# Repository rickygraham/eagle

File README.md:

# eagle
A collection of Eagle libraries and sketches!

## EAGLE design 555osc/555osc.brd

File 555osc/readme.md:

#555 Astable Oscillator

Based on 555 Timer Kit by Synthrotek

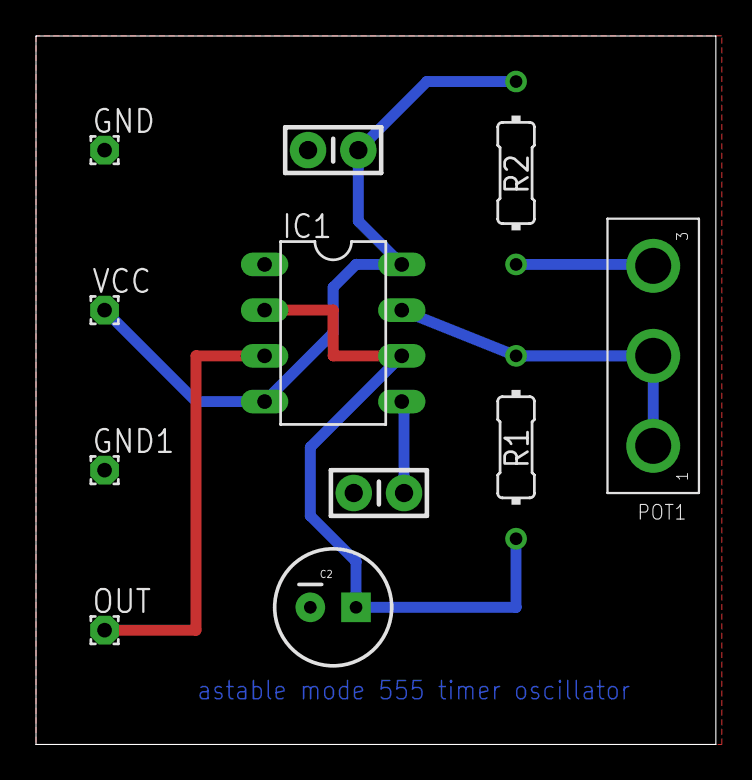
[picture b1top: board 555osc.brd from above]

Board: 2 copper layers, 37.8 x 39.4 mm, 11 parts (0 on the bottom side), 7 nets.

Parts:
C1, C3: CAP-PTH-SMALL-KIT
C2: CPOL-RADIAL-100UF-25V
GND, GND1: 1,6/0,8
IC1: ICM7555; DIL08
OUT: 1,6/0,8
POT1: POT
R1, R2: 3MM.3; RESISTOR
VCC: 1,6/0,8

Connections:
9V: C3.1, IC1.4, IC1.8, R2.2, VCC.1
GND: C1.2, C2.2, C3.2, GND.1, GND1.1, IC1.1
unnamed: POT1.3, R2.1
unnamed: C2.1, IC1.2, IC1.6, R1.1
unnamed: C1.1, IC1.5
unnamed: IC1.3, OUT.1
unnamed: IC1.7, POT1.1, POT1.2, R1.2

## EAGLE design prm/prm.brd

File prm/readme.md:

#Passive Ring Modulator

Based on Synthrotek kit:

http://www.synthrotek.com/products/lo-fi-synthesizer-circuits/passive-ring-modulator/passive-ring-mod-schematic/

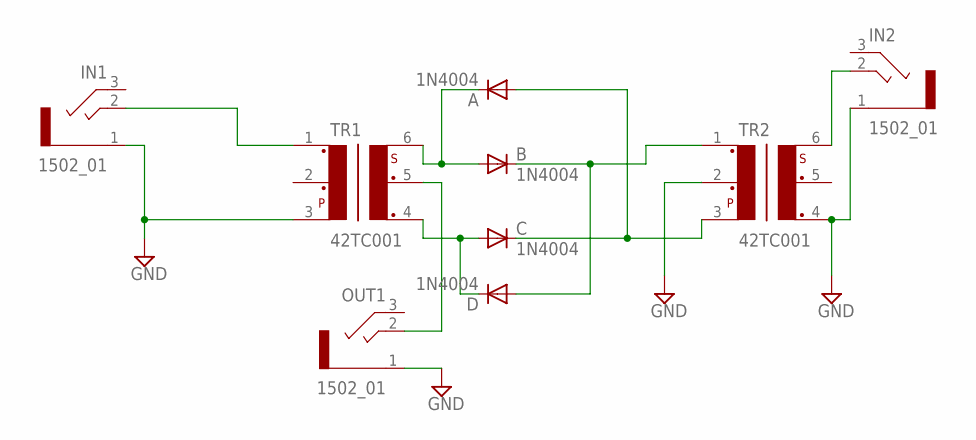
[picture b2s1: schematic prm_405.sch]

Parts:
A: 1N4004; DO41-10
B: 1N4004; DO41-10
C: 1N4004; DO41-10
D: 1N4004; DO41-10
IN1, IN2: 1502_01
OUT1: 1502_01
TR1, TR2: 42TC001; 42TC

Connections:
A: A.C, B.A, TR1.6
GND: IN1.1, IN2.1, OUT1.1, TR1.3, TR2.2, TR2.4
unnamed: IN1.2 (3), TR1.1
unnamed: OUT1.2 (3), TR1.5
unnamed: B.C, D.A, TR2.1
unnamed: A.A, C.C, TR2.3
unnamed: C.A, D.C, TR1.4
unnamed: IN2.2 (3), TR2.6

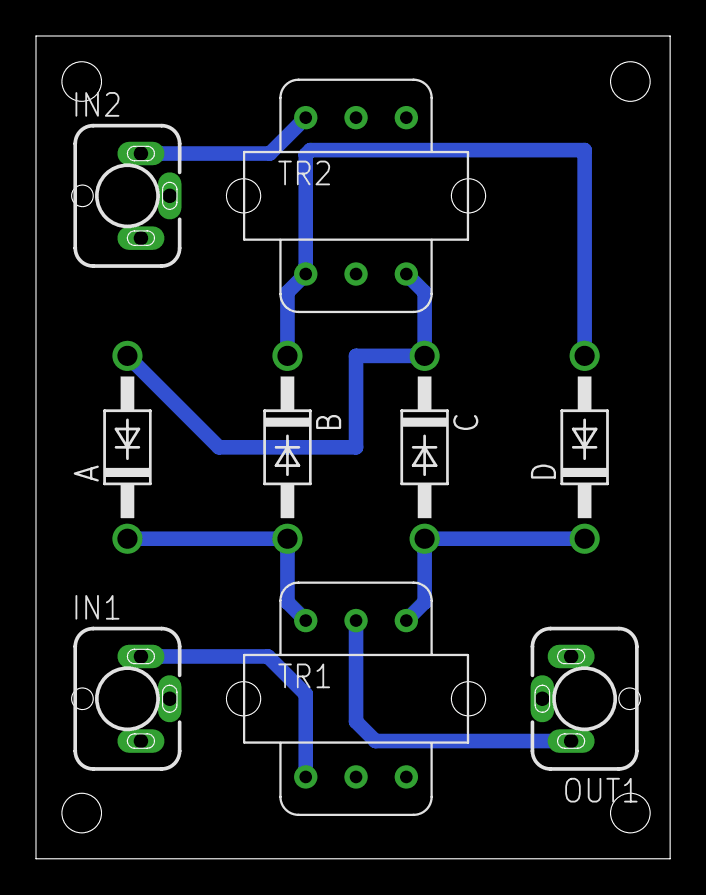
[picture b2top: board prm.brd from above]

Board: 2 copper layers, 35.2 x 45.7 mm, 9 parts (0 on the bottom side), 8 nets.

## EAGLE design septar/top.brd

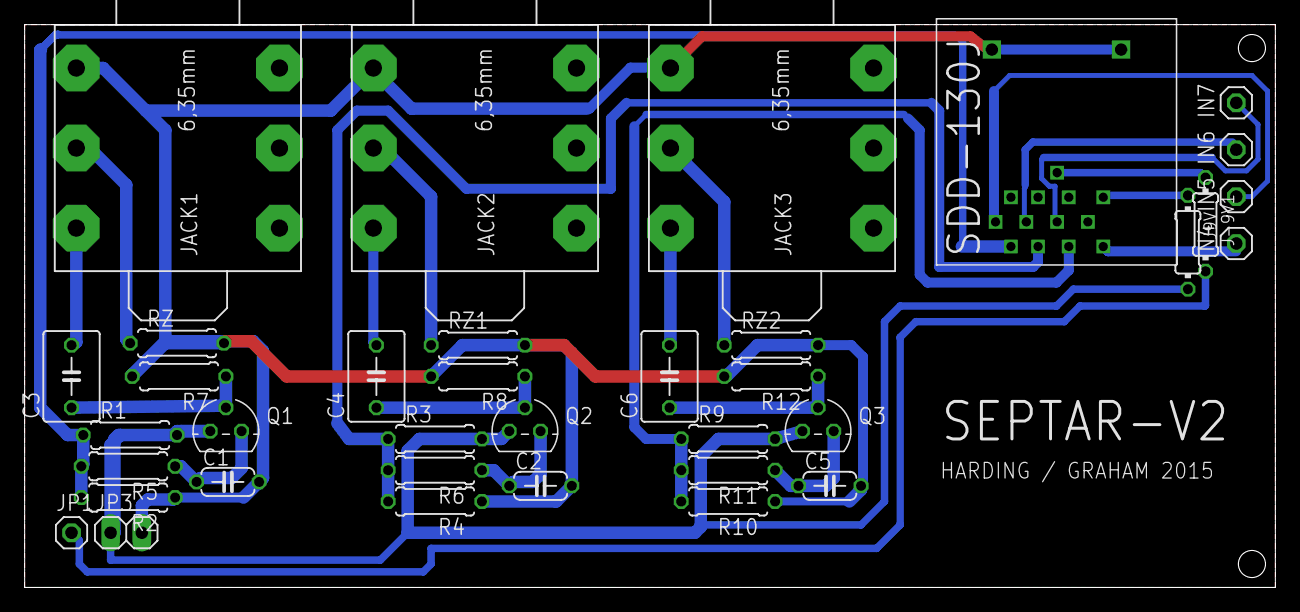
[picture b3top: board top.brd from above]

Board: 2 copper layers, 101.6 x 45.7 mm, 36 parts (0 on the bottom side), 24 nets.

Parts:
C1, C2, C5: 82pf; C050-024X044
C3, C4, C6: 1uF; C050-045X075
IN4, IN5, IN6, IN7: 1X01
J9V: 0R; 0204/7
J-9V1: 0R; 0204/7
JACK1, JACK2, JACK3: JACK_STEREO_6.35MM
JP1: -9v; 1X01
JP3: 9v; 1X02
Q1, Q2, Q3: J201; TO92
R1, R2, R3, R4, R9, R10: 2m2; 0207/7
R5, R6, R11: 10k; 0207/7
R7, R8, R12: 3k; 0207/7
RZ, RZ1, RZ2: 560r; 0207/7
U$1: 13-DIN13PINDIN; DIN-13

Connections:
GND: C1.2, C2.2, C5.2, JACK1.2, JACK2.2, JACK3.2, JP3.2, R2.1, R4.1, R7.2, R8.2, R10.1, R12.2, RZ.2, RZ1.2, RZ2.2, U$1.M1, U$1.M2
INPUT1: R1.1, R2.2, R5.2, U$1.PIN1
INPUT2: R3.1, R4.2, R6.2, U$1.PIN2
INPUT3: R9.1, R10.2, R11.2, U$1.PIN3
unnamed: IN4.1, U$1.PIN4
unnamed: C1.1, Q1.1, R5.1
unnamed: C3.1, Q1.2, R7.1
unnamed: C5.1, Q3.1, R11.1
unnamed: C3.2, JACK1.6
unnamed: JACK1.4, RZ.1
unnamed: C2.1, Q2.1, R6.1
unnamed: C4.1, Q2.2, R8.1
unnamed: IN5.1, U$1.PIN5
unnamed: C4.2, JACK2.6
unnamed: JACK2.4, RZ1.1
unnamed: IN6.1, U$1.PIN6
unnamed: C6.1, Q3.2, R12.1
unnamed: C6.2, JACK3.6
unnamed: JACK3.4, RZ2.1
unnamed: IN7.1, U$1.PIN7
unnamed: J9V.1, U$1.PIN12
unnamed: J-9V1.2, JP1.1
unnamed: J-9V1.1, U$1.PIN13
VCC: J9V.2, JP3.1, Q1.3, Q2.3, Q3.3, R1.2, R3.2, R9.2

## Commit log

2016-02-29 Added files via upload
    The first Septar beta-testers requested a rectangular DIN socket (sdd-130j). I couldn’t find a 13-pin DIN library for Eagle, so I made one for Septar V2.
2016-02-29 Added files via upload
    Passive Ring Modulator, based on:
    http://www.synthrotek.com/products/lo-fi-synthesizer-circuits/passive-ring-modulator/passive-ring-mod-schematic/
2016-02-29 Added files via upload
2016-07-05 Create 555osc

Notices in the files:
parts and their libraries:
SparkFun-Capacitors: Licensing: Creative Commons ShareAlike 4.0 International - https://creativecommons.org/licenses/by-sa/4.0
